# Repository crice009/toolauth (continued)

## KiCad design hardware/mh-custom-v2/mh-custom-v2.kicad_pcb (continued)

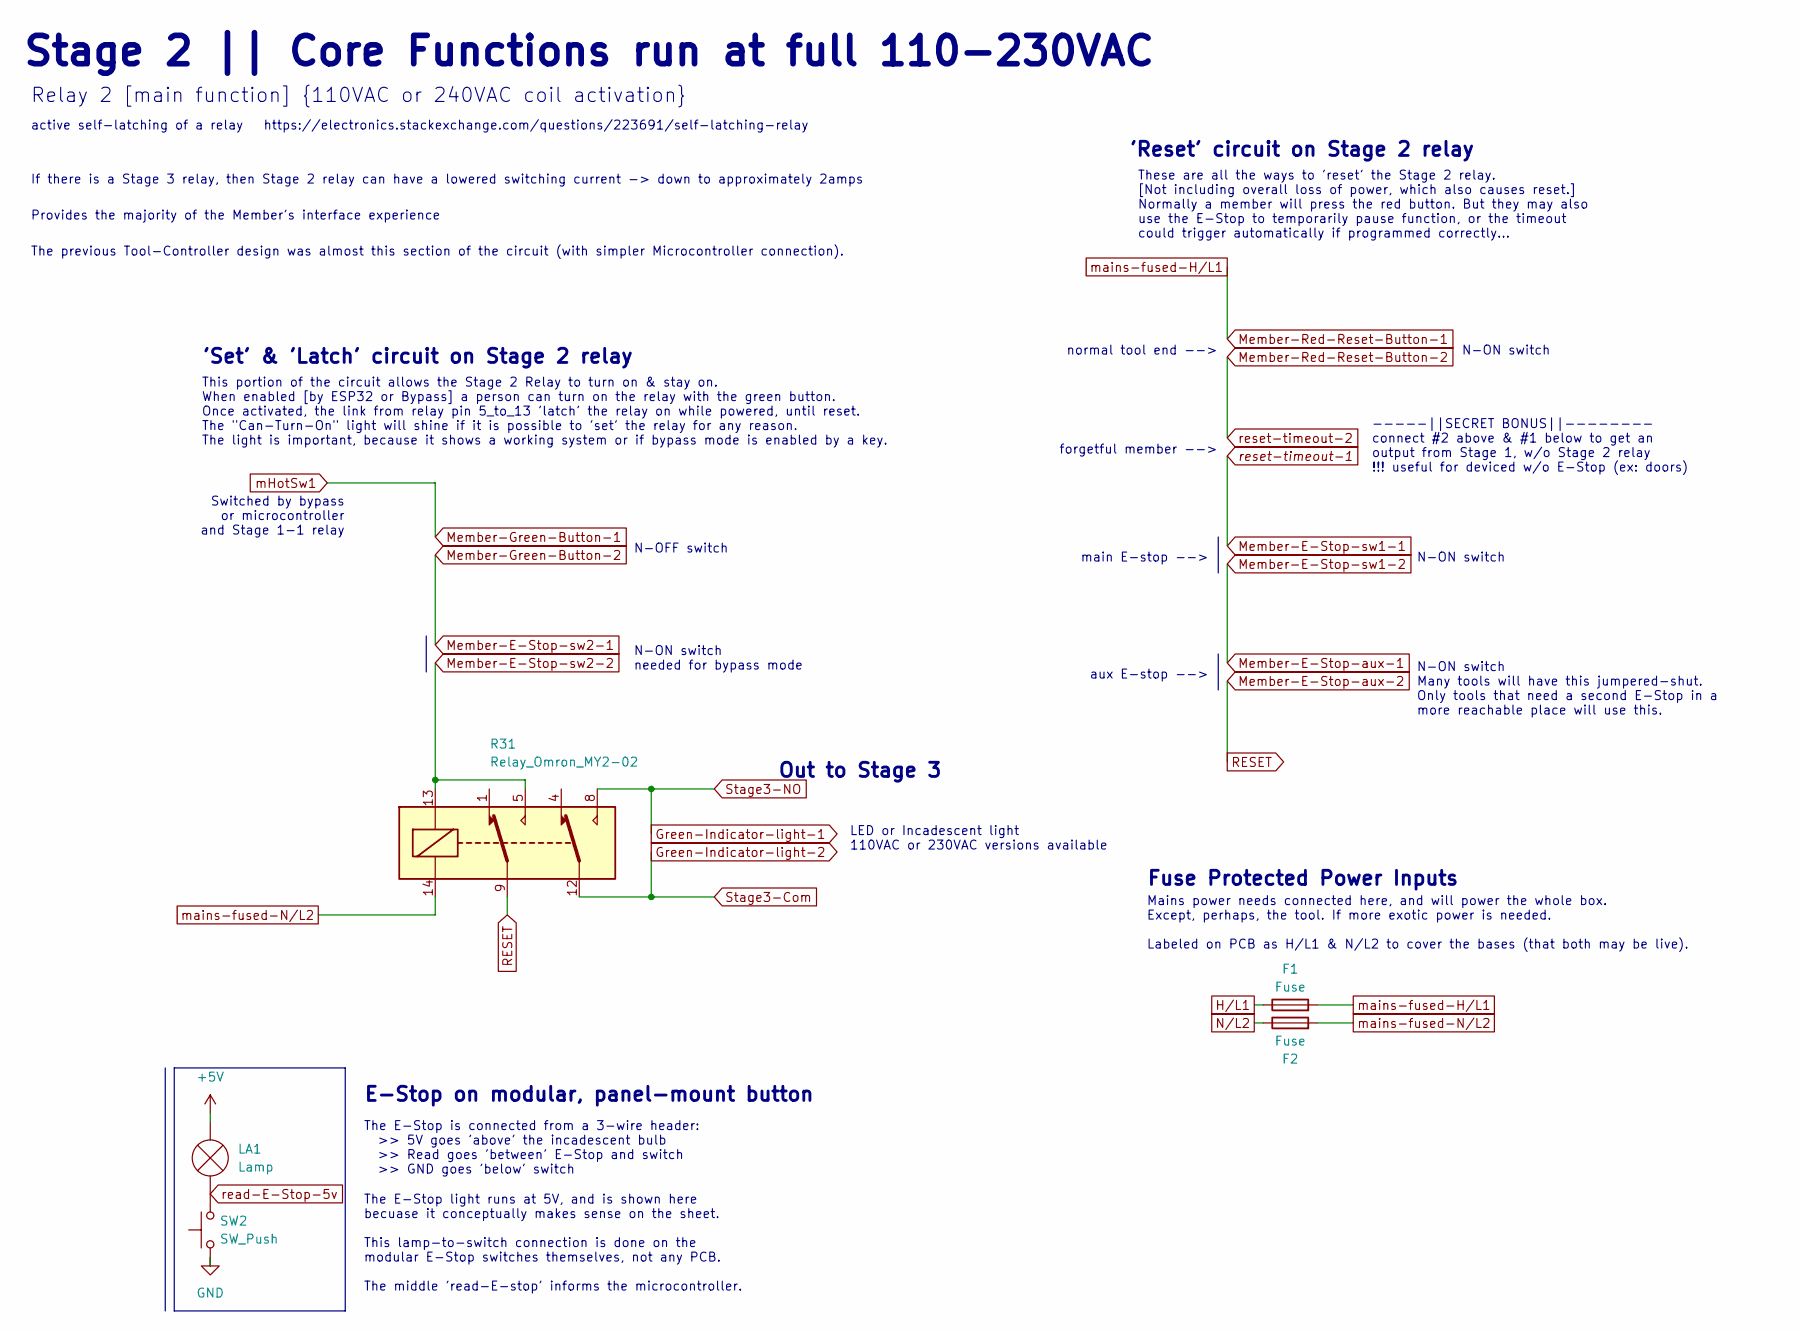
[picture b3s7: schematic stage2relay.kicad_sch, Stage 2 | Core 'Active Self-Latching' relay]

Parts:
F1: Fuse; Fuseholder_Cylinder-5x20mm_Stelvio-Kontek_PTF78_Horizontal_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; JLCPCB Part # C717030
F2: Fuse; Fuseholder_Cylinder-5x20mm_Stelvio-Kontek_PTF78_Horizontal_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
LA1: Lamp
R31: Relay_Omron_MY2-02; relay-Omron-MY2-02
SW2: SW_Push

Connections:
Green-Indicator-light-1: R31.8; also elsewhere on the board
Green-Indicator-light-2: R31.12; also elsewhere on the board
H/L1: F1.1; also elsewhere on the board
Member-E-Stop-aux-2: R31.9; also elsewhere on the board
Member-E-Stop-sw2-2: R31.5, R31.13; also elsewhere on the board
Member-Red-Reset-Button-1: F1.2; also elsewhere on the board
unnamed: LA1.1 (-), SW2.2
N/L2: F2.1; also elsewhere on the board
mains-fused-N/L2: F2.2, R31.14; also elsewhere on the board

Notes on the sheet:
Switched by bypass or microcontroller and Stage 1-1 relay
The previous Tool-Controller design was almost this section of the circuit (with simpler Microcontroller connection).
normal tool end -->
Mains power needs connected here, and will power the whole box. Except, perhaps, the tool. If more exotic power is needed. Labeled on PCB as H/L1 & N/L2 to cover the bases (that both may be live).
'Reset' circuit on Stage 2 relay
Stage 2 || Core Functions run at full 110-230VAC
If there is a Stage 3 relay, then Stage 2 relay can have a lowered switching current -> down to approximately 2amps
The E-Stop light runs at 5V, and is shown here becuase it conceptually makes sense on the sheet. This lamp-to-switch connection is done on the modular E-Stop switches themselves, not any PCB. The middle 'read-E-stop' informs the microcontroller.
aux E-stop -->
The E-Stop is connected from a 3-wire header: >> 5V goes 'above' the incadescent bulb >> Read goes 'between' E-Stop and switch >> GND goes 'below' switch
main E-stop -->
N-OFF switch
E-Stop on modular, panel-mount button
N-ON switch
These are all the ways to 'reset' the Stage 2 relay. [Not including overall loss of power, which also causes reset.] Normally a member will press the red button. But they may also use the E-Stop to temporarily pause function, or the timeout could trigger automatically if programmed correctly...
forgetful member -->
N-ON switch needed for bypass mode
active self-latching of a relay https://electronics.stackexchange.com/questions/223691/self-latching-relay
Fuse Protected Power Inputs
'Set' & 'Latch' circuit on Stage 2 relay
LED or Incadescent light 110VAC or 230VAC versions available
N-ON switch Many tools will have this jumpered-shut. Only tools that need a second E-Stop in a more reachable place will use this.
Relay 2 [main function] {110VAC or 240VAC coil activation}
Out to Stage 3
Provides the majority of the Member's interface experience
This portion of the circuit allows the Stage 2 Relay to turn on & stay on. When enabled [by ESP32 or Bypass] a person can turn on the relay with the green button. Once activated, the link from relay pin 5_to_13 'latch' the relay on while powered, until reset. The "Can-Turn-On" light will shine if i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
-----||SECRET BONUS||-------- connect #2 above & #1 below to get an output from Stage 1, w/o Stage 2 relay !!! useful for deviced w/o E-Stop (ex: doors)

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
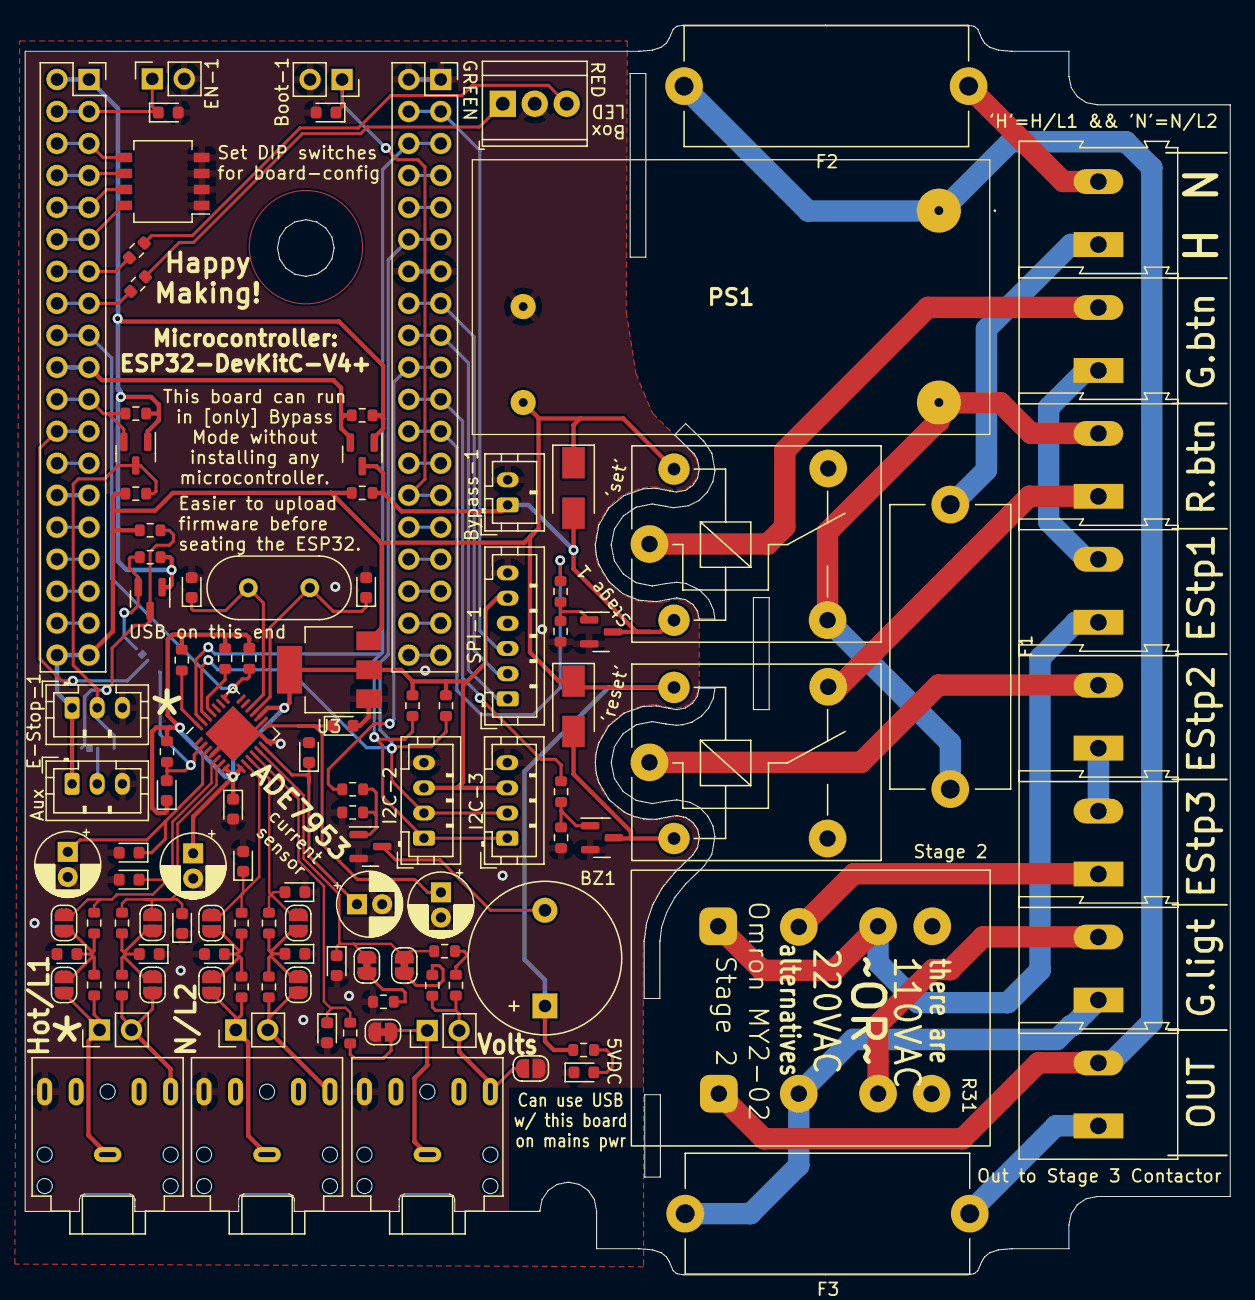
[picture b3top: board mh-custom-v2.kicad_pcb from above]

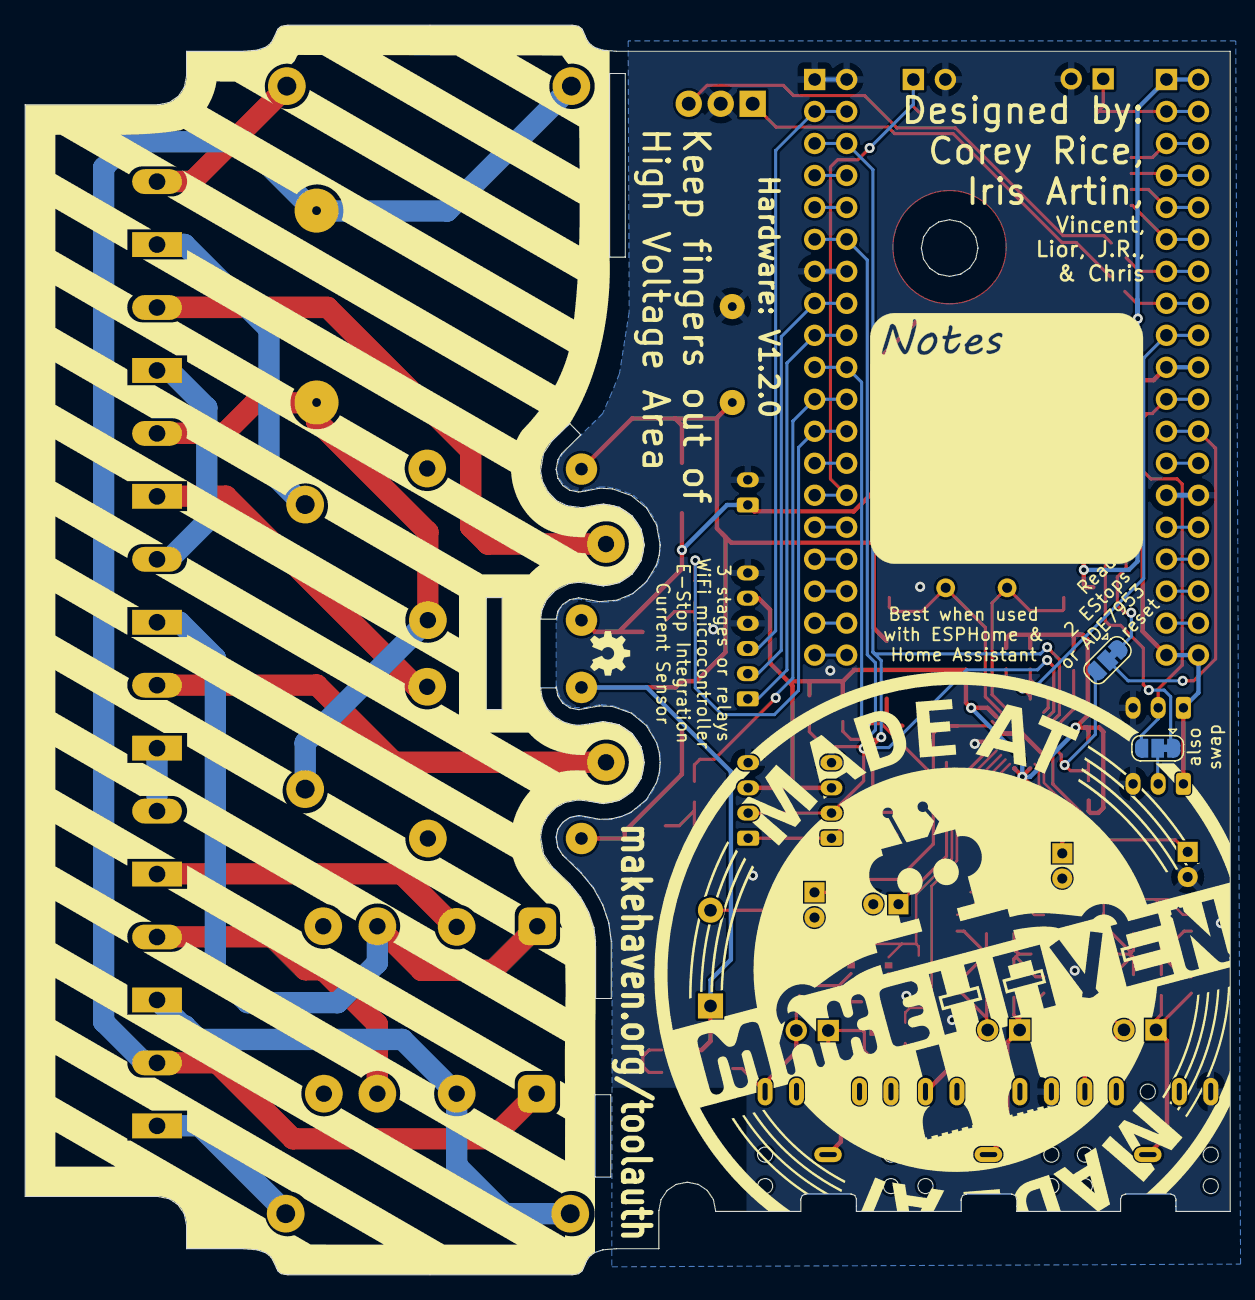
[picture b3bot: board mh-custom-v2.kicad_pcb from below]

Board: 2 copper layers, 95.7 x 99.3 mm, 117 parts (2 on the bottom side), 91 nets.

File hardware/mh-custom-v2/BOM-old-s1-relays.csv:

Comment,Designator,Footprint,JLCPCB Part #
SANYOU_SRD_Form_C,"5vRelay1-1,5vRelay1-2",Relay_THT:Relay_SPDT_SANYOU_SRD_Series_Form_C,C35449
Buzzer,BZ1,Buzzer_Beeper:Buzzer_15x7.5RM7.6,C96095
Conn_01x02_Female,Bypass-1,Connector_JST:JST_PH_B2B-PH-K_1x02_P2.00mm_Vertical,C131337
0.1uF,"C1,C2",LED_SMD:LED_0603_1608Metric,C14663
100nF,"C13,C16,C17,C22",LED_SMD:LED_0603_1608Metric,C14663
10uF,C14,Capacitor_THT:CP_Radial_D5.0mm_P2.00mm,C88726
1uF,C15,LED_SMD:LED_0603_1608Metric,C15849
4.7uF,"C18,C19,C23",Capacitor_THT:CP_Radial_D5.0mm_P2.00mm,C88759
20pF,"C20,C21",LED_SMD:LED_0603_1608Metric,C1648
33nF,"C3,C4,C5,C6,C7,C8,C9,C10,C11,C12",LED_SMD:LED_0603_1608Metric,C21117
LED,D2,LED_SMD:LED_0603_1608Metric,C2286
B160-E3,"D3,D4",Diode_SMD:D_SMA,C24784
Conn_01x03_Female,E-Stop-1,Connector_JST:JST_PH_B3B-PH-K_1x03_P2.00mm_Vertical,C131339
Fuse,"F1,F2,F3",Fuse:Fuseholder_Cylinder-5x20mm_Stelvio-Kontek_PTF78_Horizontal_Open,C717030
Conn_01x04_Female,"I2C-1,I2C-2,I2C-3",Connector_JST:JST_PH_B4B-PH-K_1x04_P2.00mm_Vertical,C131334
H/L1,IN-1,Connector_Audio:Jack_3.5mm_CUI_SJ1-3525N_Horizontal,C692542
N/L2,IN-2,Connector_Audio:Jack_3.5mm_CUI_SJ1-3525N_Horizontal,C692542
VOLTS,IN-3,Connector_Audio:Jack_3.5mm_CUI_SJ1-3525N_Horizontal,C692542
Conn_01x03_Male,J1,TerminalBlock_TE-Connectivity:TerminalBlock_TE_282834-3_1x03_P2.54mm_Horizontal,C557686
Conn_02x19_Top_Bottom,"J3,J4",Connector_PinSocket_2.54mm:PinSocket_2x19_P2.54mm_Vertical,C2897420
Screw_Terminal_01x04,"J5,J6,J7,J8",TerminalBlock:TerminalBlock_Altech_AK300-4_P5.00mm,C192769
1k,"R1,R5,R6,R14,R15,R16,R17,R18,R20,R21,R26,R27,R29",Resistor_SMD:R_0603_1608Metric,C21190
499k,"R13,R19",Resistor_SMD:R_0603_1608Metric,C131054
10k,"R2,R3,R4,R22,R23,R24,R25,R28,R30,R32,R33",Resistor_SMD:R_0603_1608Metric,C25804
10kOhm,"R7,R8",Resistor_SMD:R_0603_1608Metric,C25804
100,"R9,R10,R11,R12",Resistor_SMD:R_0603_1608Metric,C22775
Conn_01x06_Female,SPI-1,Connector_JST:JST_PH_B6B-PH-K_1x06_P2.00mm_Vertical,C131342
SW_DIP_x04,SW1,Button_Switch_SMD:SW_DIP_SPSTx04_Slide_Omron_A6H-4101_W6.15mm_P1.27mm,C224996
AO3400A,"T1,T2,T3,T4,T5",Package_TO_SOT_SMD:SOT-23,C427382
ADE7953xCP,U2,Package_CSP:LFCSP-28-1EP_5x5mm_P0.5mm_EP3.14x3.14mm,C515890
3.58MHz,Y1,Crystal:Crystal_HC49-4H_Vertical,C2826865

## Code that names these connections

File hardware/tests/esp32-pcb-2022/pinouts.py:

import asyncio
from machine import Pin, PWM #should this be 'Board' in the new Python?
import neopixel
import countio 
from analogio import AnalogIn



#-------------------------------------------------------------------------
class PCB(object):
    def __init__(self, edition):
        edition = edition

    def __repr__(self):
        return f"PCB({self.edition})"

    def checkConfig(self):
        d = bin(0)
        for sw in self.dips:
            d << 1
            state = sw.value()
            d = d + state
        self.configDec = int(d) #pin 1 is the MSB

    def configMessage(self):    
        d = self.configDec
        if d==0:    #0000 -- pin order: 1234 | sw to the right is a '1'
            self.config="E-Stop | 110VAC S2 Relay | 440VAC 3PH Contactor"
        elif d==1:  #0001
            self.config="E-Stop | 230VAC S2 Relay | 230VAC 3PH Contactor"
        elif d==2:  #0010
            self.config="E-Stop | 230VAC S2 Relay | 230VAC 1PH Contactor"
        elif d==3:  #0011
            self.config="E-Stop | 230VAC S2 Relay | 208VAC 3PH Contactor"
        elif d==4:  #0100
            self.config="E-Stop | 230VAC S2 Relay | 208VAC 1PH Contactor"
        elif d==5:  #0101
            self.config="E-Stop | 110VAC S2 Relay | 110VAC 1PH Contactor"
        elif d==6:  #0110
            self.config="E-Stop | 230VAC S2 Relay | NO S3 Contactor"
        elif d==7:  #0111
            self.config="E-Stop | 110VAC S2 Relay | NO S3 Contactor"
        elif d==8:  #1000
            self.config="NO E-Stop | No S2 relay | <5 Amps doors and switches"
        elif d==9:  #1001
            self.config="NO E-Stop | 110VAC S2 relay | <10 Amps very safe tools"
        elif d==10: #1010
            self.config="invalid DIP switch entry..."
        elif d==11: #1011
            self.config="invalid DIP switch entry..."
        elif d==12: #1100
            self.config="invalid DIP switch entry..."
        elif d==13: #1101
            self.config="invalid DIP switch entry..."
        elif d==14: #1110
            self.config="invalid DIP switch entry..."
        elif d==15: #1111
            self.config="invalid DIP switch entry..."
    
    @asyncio.coroutine
    def setS1Relay(self, delay): #probably a few seconds so members can press the green button
        self.set_s1.ON()
        asyncio.sleep(delay)
        self.set_s1.OFF()

    @asyncio.coroutine
    def tone(self, freq, duration):
        beeper = PWM(self.buzz, freq=freq, duty=512)
        asyncio.sleep(duration)
        beeper.deinit()   

    def getS1Relay(self):
        return self.read_s1.value()

    def getBypass(self):
        bp = self.readBypass.value()
        s1r= self.s1RelayState()
        if bp==0 and s1r==0:
            state=1
        else:
            state=0
        return state

    def getEStop(self): #synchronous
        return self.readEstop()

    def autoEstop(self): #https://learn.adafruit.com/cooperative-multitasking-in-circuitpython-with-asyncio/handling-interrupts
        with countio.Counter(self.readEstop) as interrupt:
            if interrupt.count > 0:
                #send some sort of a log that E-Stop was pressed | this may automatically work?
                interrupt.count = 0

    def armEstop(self): #autoEstop and armEstop are my first guess. we'll have to test them...
        asyncio.create_task(self.autoEstop())

    def getCurrentDigital(self): #returns a 1 or 0
        return self.current.digital.value()

    def getCurrentAnalog(self): #returns a float for "percentage measurable current"
        return float((self.current.analog.value * 100) / 65536)

    @asyncio.coroutine
    def setTimeout(self):
        self.timeout.ON()
        asyncio.sleep(0.25)
        self.timeout.OFF()

    @asyncio.coroutine      #as written, this will auto-timeout after 5 minutes of "no tool current" but idk about that digital threshold... needs testing
    def autoTimeout(self):  #this feels like it is ripe for some monads, and more elegance, but idk how to do that...
        asyncio.sleep(5*60)
        if not self.getCurrentDigital():
            self.setTimeout()
            return
        self.autoTimeout()
        return

    @asyncio.coroutine
    def currentUseLogging(self):
        if not self.getEstop(): #will only work with a normal card swipe, until E-Stop is used
            draw = self.getCurrentAnalog()
            #somehow send this to a logging system
            asyncio.sleep(0.1)
            self.currentUseLogging()

#-------------------------------------------------------------------------
#
#       Above we have defined many of the mid-level logic functions
#
#       Below we instantiate the "PCB" to match the physical hardware of the board
#
#-------------------------------------------------------------------------


pcb = PCB("july_2022_CoreyRice")

# All props are set to GPIO pins for ESP32
# devkitc-v4 (board) pins are commented just in case

#SPI communication (with PN532 card reader)
pcb.spi.pico = 23 #[I/O] devkitc_pin_21
pcb.spi.poci = 19 #[I/O] devkitc_pin_27
pcb.spi.sck  = 18 #[I/O] devkitc_pin_28
pcb.spi.cs   =  5 #[I/O] devkitc_pin_29

#I2C communication (with LCD screen or backup for PN532 card reader)
pcb.i2c.sda  = 21 #[I/O] devkitc_pin_25
pcb.i2c.scl  = 22 #[I/O] devkitc_pin_22

#pin to activate Stage 1 relay & begin tool turn-on process 
pcb.set_s1 = Pin(16, Pin.OUT) #devkitc_pin_31 --output
pcb.read_s1 = Pin(17, Pin.IN) #devkitc_pin_30 --intput

#addressable LEDs for user feedback
pixel_pin=15 #devkitc_pin_35
pcb.numPixel = 2 #how many neoPixels
pcb.pixels = neopixel.NeoPixel(pixel_pin, pcb.numPixel, brightness=0.9, auto_write=False)
pcb.pixels.fill((255,0,0))
pcb.pixels.show()

#read state of E-Stop button [LOW means e-stop in use]
pcb.readEstop = Pin(14, Pin.IN) #devkitc_pin_12
pcb.armEstop() #so it will send a log when E-Stop pressed (if it works)

#can be used to shut-off/reset the tool
pcb.timeout = Pin(27, Pin.OUT) # devkitc_pin_11

#check the state of the bypass key
pcb.readBypass = Pin(26, Pin.IN) #devkitc_pin_10
#--------note: only truly bypass if readBypass:LOW && read_s1:LOW

#drive the buzzer for audio feedback
pcb.buzz = Pin(25, Pin.OUT) #devkitc_pin_9
pcb.tone(280, 0.25) #short sound to check it is working

#current sensor to monitor tool use
pcb.current.digital = Pin(35, Pin.IN) #devkitc_pin_6
pcb.current.analog  = AnalogIn(34) #devkitc_pin_5 | values 0-65536

# the dip pins that can give feedback for hardware versions
pcb.dips = [Pin(36, Pin.IN), #1
            Pin(39, Pin.IN), #2
            Pin(32, Pin.IN), #3
            Pin(33, Pin.IN)] #4  |devkitc_pins_vp,vn,32,33
pcb.checkConfig()
pcb.configMessage()

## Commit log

2022-09-11 fixing gitignore
2022-09-11 continue to fix gitignore
2022-09-11 touching things up after noticing an unexpected postman result
2022-09-11 added findkeys, templates and separated views to new file
2022-09-11 change findkeys decorator to fit norms
2022-09-11 things mostly working at MakeHaven
2022-09-11 fix(__init__): listen on all interfaces
2022-09-11 got things working with Vincent
2022-09-11 hacking a solution for the tech demo
2022-09-11 testing connections renamed firmware to 'door'
2022-09-12 isolate and fixing server errors. only namespace errors remain
2022-09-12 developing ideas for mroe functions
2022-09-12 configuration in crud
2022-09-12 added uuid and better Exception handling
2022-09-12 specific messages in Exceptions
2022-09-12 toubleshooting
2022-09-12 dict to string
2022-09-13 server seems to work - ESP32 sometimes hangs on slow responses
2022-09-13 try abort instead of return abort
2022-09-13 comment out code
2022-09-13 chore(everything): autoformat...EVERYTHING
2022-09-13 chore(pyproject): add black
2022-09-13 chore(crud,templates): remove unused files
2022-09-13 added experimental threading wrapper
2022-09-13 changed /authreq to be a multithreaded function
2022-09-13 refactor(data,models,views): rename data to models
2022-09-13 refactor(views): remove unused imports
2022-09-13 oops, fixing the thread attempt
2022-09-13 refactor(views): remove comments
2022-09-14 refactor(views): typings and named parameters
2022-09-14 refactor(views): reduce nesting
2022-09-14 refactor(authorized, models): simplify authreq function and update documentation to be friendly with docs generator
2022-09-14 refactor(views): further simplify documentation
2022-09-14 refactor(esphome_api): improve readability of device_enable
2022-09-14 refactor(esphome_api,readtotool): improve readability of other_picked and readtotool
2022-09-14 chore(toolauth): add Hypermodern Python cookiecutter
2022-09-16 refactor(api): make api more similar to cardsystem
2022-09-16 (esphome_api) added tool_com_error function
2022-09-16 (readtotool) added error handler that notifies card reader when tool is absent
2022-09-16 slightly better homepage
2022-09-16 (views) removed incorrect 'other_picked' route and added notes for how to add it in to the session_handler
2022-09-19 updating api key and including bridgeport on tooltoreader.yaml
2022-09-20 style rules: black
2022-09-20 maknig some progress in passing a session object
2022-09-21 added sqlite3 database functions
2022-09-21 added 'poetry run init_db' command
2022-09-21 added explicit 'get()' to SessionIn class
2022-09-21 added other_tool_picked and threaded version
2022-09-21 added more robust handling of other_picked, not tested
2022-09-21 added database
2022-09-21 tried to start a config file
2022-09-21 simple script to start/restart database
2022-09-22 views needed _connect_db imported
2022-09-25 added the only versions of hardware design remaining after laptop died :(
2022-09-25 another hardware save from the sad loss of laptop :(
2022-09-26 redesign v2 board from saved parts
2022-09-28 low-voltage side of V2 board rebuilt. Started on high-voltage side
2022-10-03 change of license
2022-10-03 approaching ordering from JLCPCB
2022-10-03 prepping for JLCPCB order - all parts listed with numbers, BOM generated
2022-10-05 finalizing details of ordering from JLCPCB
2022-10-06 improved some of the connections for easier soldering/production
2022-10-07 laptop back, coordinating efforts
2022-10-07 back up recovered kicad footprints
2022-10-07 added linear regulator for 3.3V peripherals and ADE7953 reset jumper
2022-10-08 after lots of testing, found we need 2.2k resistors for I2C pullup
2022-10-08 added jumpers that allow for two seperate E-Stop readings
2022-10-09 b-silkscreen fixed
2022-10-09 applied workaround for 3.3v and 3v3 known bug: https://gitlab.com/kicad/libraries/kicad-symbols/-/issues/3153
2022-10-10 just ordered from JLCPCB
2022-10-13 restarting work on the server
2022-10-13 update gitignore
2022-10-13 vscode settings
2022-11-27 speedrun, first commit
2022-11-27 added logfile
2022-12-02 deleted hardware | ref: https://github.com/crice009/toolauth-hardware
2022-12-02 added logo and link to hardware repo
2022-12-03 another copy from speedrun-original~
2022-12-04 cleaned the directory, and verified it works.
2022-12-04 cleaned directory, verified changes staged, should work...
2022-12-04 recover the 403 error - had it in a 500 wrapper before
2022-12-04 and session_event 403 error
2022-12-04 improved error handling in esphome_api
2022-12-04 esphome_api errors clarified to 504 when not able to connecct to ESP32s
2022-12-04 all-important logo
2022-12-04 added dockerfile
2022-12-04 dokerfile | directed to 'run' function in __inti_.py
